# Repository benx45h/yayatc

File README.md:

# YAYATC- Yet Another YATC
### A new temperature controller, because the YATC links were broken.

YAYATC is a temperature controller designed to heat or cool things to any temperature, within reason. YAYATC can handle either a 10k NTC thermistor or the 1-wire thing from Sparkfun as a temperature sensor. As long as only one is plugged in, YAYATC will automatically detect which to use.
No external power supply is needed- all circuitry is powered directly from the wall.  

The goal here was to minimize design time, and other temperature controllers may have better performance, cheaper BOMs, easier assembly, etc.

Revision 1 has not been tested. If you want to make one anyways, go ahead.

Revision 1 known issues:
~~ - No way to tell if temperature is positive or negative ~~  
~~ - Only 2 digits. No way to display temperatures above 100. ~~

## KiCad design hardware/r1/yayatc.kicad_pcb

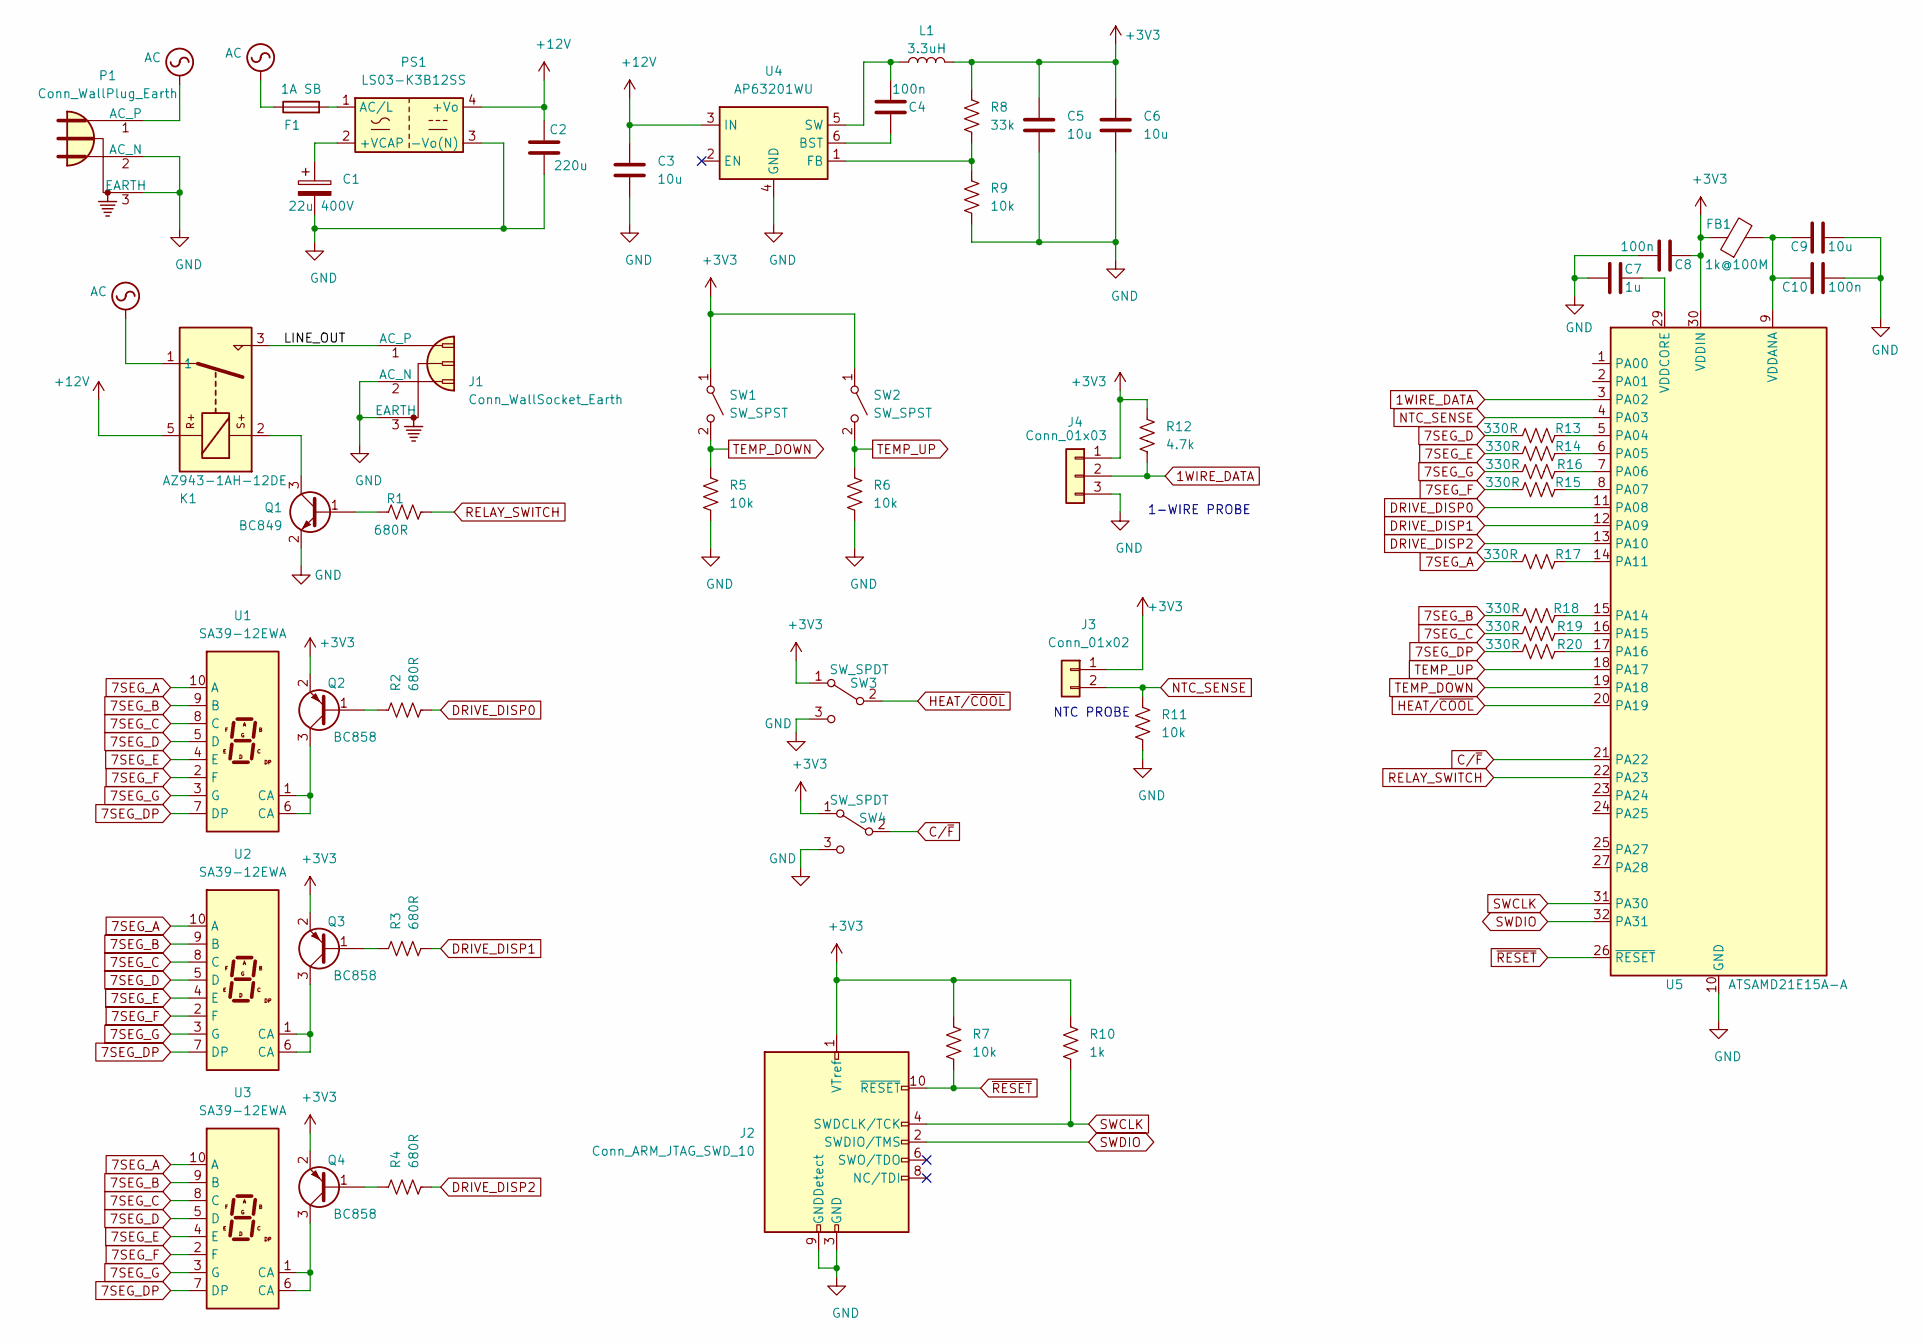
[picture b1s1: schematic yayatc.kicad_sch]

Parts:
C1: 22u 400V; CP_Radial_D12.5mm_P5.00mm; Digikey-PN 493-5875-ND
C2: 220u; CP_Radial_D6.3mm_P2.50mm; Digikey-PN 732-8797-1-ND
C3, C5, C6, C9: 10u; C_0805_2012Metric_Pad1.18x1.45mm_HandSolder; Digikey-PN 1276-6455-1-ND
C4, C8, C10: 100n; C_0603_1608Metric_Pad1.08x0.95mm_HandSolder; Digikey-PN 1276-CL10B104KB8NNNLCT-ND
C7: 1u; C_0603_1608Metric_Pad1.08x0.95mm_HandSolder; Digikey-PN 1276-1102-1-ND
F1: 1A SB; 0697H1000-02; Digikey-PN 507-1927-1-ND
FB1: 1k@100M; L_0603_1608Metric_Pad1.05x0.95mm_HandSolder; Digikey-PN 587-1895-1-ND
J1: Conn_WallSocket_Earth; SolderWire-1sqmm_1x03_P5.4mm_D1.4mm_OD2.7mm; Digikey-PN Q337-ND
J2: Conn_ARM_JTAG_SWD_10; PinHeader_2x05_P1.27mm_Vertical; Digikey-PN 1849-PR20B05VBDN-ND
J3: Conn_01x02; JST_PH_B2B-PH-K_1x02_P2.00mm_Vertical; Digikey-PN 455-1704-ND
J4: Conn_01x03; JST_PH_B3B-PH-K_1x03_P2.00mm_Vertical; Digikey-PN 455-1704-ND
K1: AZ943-1AH-12DE; Relay_AZ945_A; Digikey-PN 2487-AZ943-1AH-12DE-ND
L1: 3.3uH; L_0805_2012Metric_Pad1.15x1.40mm_HandSolder; Digikey-PN 445-6759-1-ND
P1: Conn_WallPlug_Earth; 703W-00-54; Digikey-PN Q220-ND
PS1: LS03-K3B12SS; LSxx-K3BxxSS; Digikey-PN 2725-LS03-K3B12SS-ND
Q1: BC849; SOT-23; Digikey-PN BC849B-TPMSCT-ND
Q2, Q3, Q4: BC858; SOT-23; Digikey-PN BC858CLT3GOSCT-ND
R1, R2, R3, R4: 680R; R_0603_1608Metric_Pad0.98x0.95mm_HandSolder; Digikey-PN RR08P680DCT-ND
R5, R6, R7, R9, R11: 10k; R_0603_1608Metric_Pad0.98x0.95mm_HandSolder; Digikey-PN RR08P10.0KDCT-ND
R8: 33k; R_0603_1608Metric_Pad0.98x0.95mm_HandSolder; Digikey-PN 311-33.0KHRCT-ND
R10: 1k; R_0603_1608Metric_Pad0.98x0.95mm_HandSolder; Digikey-PN RR08P1.0KDCT-ND
R12: 4.7k; R_0603_1608Metric_Pad0.98x0.95mm_HandSolder; Digikey-PN 311-4.70KHRCT-ND
R13, R14, R15, R16, R17, R18, R19, R20: 330R; R_0603_1608Metric_Pad0.98x0.95mm_HandSolder; Digikey-PN 311-330HRCT-ND
SW1, SW2: SW_SPST; SW_PUSH_6mm_H13mm; Digikey-PN 450-1642-ND
SW3, SW4: SW_SPDT; OS102011MS2Q*; Digikey-PN CKN9565-ND
U1, U2, U3: SA39-12EWA; Sx39-1xxxxx; Digikey-PN 3011-SA39-12EWA-ND
U4: AP63201WU; TSOT-23-6; Digikey-PN 31-AP62301Z6-7CT-ND
U5: ATSAMD21E15A-A; TQFP-32_7x7mm_P0.8mm; Digikey-PN ATSAMD21E17L-AFTCT-ND

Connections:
1WIRE_DATA: J4.2, R12.2, U5.3 (PA02)
7SEG_A: R17.1, U1.10 (A), U2.10 (A), U3.10 (A)
7SEG_B: R18.1, U1.9 (B), U2.9 (B), U3.9 (B)
7SEG_C: R19.1, U1.8 (C), U2.8 (C), U3.8 (C)
7SEG_D: R13.1, U1.5 (D), U2.5 (D), U3.5 (D)
7SEG_DP: R20.1, U1.7 (DP), U2.7 (DP), U3.7 (DP)
7SEG_E: R14.1, U1.4 (E), U2.4 (E), U3.4 (E)
7SEG_F: R15.1, U1.2 (F), U2.2 (F), U3.2 (F)
7SEG_G: R16.1, U1.3 (G), U2.3 (G), U3.3 (G)
+3V3: C5.1, C6.1, C8.1, FB1.1, J2.1 (VTref), J3.1, J4.1, L1.2, Q2.2 (E), Q3.2 (E), Q4.2 (E), R7.1, R8.1, R10.1, R12.1, SW1.1 (A), SW2.1 (A), SW3.1 (A), SW4.1 (A), U5.30 (VDDIN)
+12V: C2.1, C3.1, K1.5, PS1.4 (+Vo), U4.3 (IN)
/LINE_OUT: J1.1 (AC_P), K1.3
AC: F1.1, K1.1, P1.1 (AC_P)
C/~F: SW4.2 (B), U5.21 (PA22)
DRIVE_DISP0: R2.2, U5.11 (PA08)
DRIVE_DISP1: R3.2, U5.12 (PA09)
DRIVE_DISP2: R4.2, U5.13 (PA10)
GND: C1.2, C2.2, C3.2, C5.2, C6.2, C7.1, C8.2, C9.2, C10.2, J1.2 (AC_N), J1.3 (EARTH), J2.3 (GND), J2.5 (GND), J2.9 (GNDDetect), J4.3, P1.2 (AC_N), P1.3 (EARTH), PS1.3 (-Vo(N)), Q1.2 (E), R5.2, R6.2, R9.2, R11.2, SW3.3 (C), SW4.3 (C), U4.4 (GND), U5.10 (GND), U5.28 (GND)
HEAT/~COOL: SW3.2 (B), U5.20 (PA19)
NTC_SENSE: J3.2, R11.1, U5.4 (PA03)
unnamed: C1.1, PS1.2 (+VCAP)
unnamed: C4.1, U4.6 (BST)
unnamed: C4.2, L1.1, U4.5 (SW)
unnamed: C7.2, U5.29 (VDDCORE)
unnamed: C9.1, C10.1, FB1.2, U5.9 (VDDANA)
unnamed: F1.2, PS1.1 (AC/L)
unnamed: K1.2, Q1.3 (C)
unnamed: Q1.1 (B), R1.1
unnamed: Q2.1 (B), R2.1
unnamed: Q2.3 (C), U1.1 (CA), U1.6 (CA)
unnamed: Q3.1 (B), R3.1
unnamed: Q3.3 (C), U2.1 (CA), U2.6 (CA)
unnamed: Q4.1 (B), R4.1
unnamed: Q4.3 (C), U3.1 (CA), U3.6 (CA)
unnamed: R8.2, R9.1, U4.1 (FB)
unnamed: R13.2, U5.5 (PA04)
unnamed: R14.2, U5.6 (PA05)
unnamed: R15.2, U5.8 (PA07)
unnamed: R16.2, U5.7 (PA06)
unnamed: R17.2, U5.14 (PA11)
unnamed: R18.2, U5.15 (PA14)
unnamed: R19.2, U5.16 (PA15)
unnamed: R20.2, U5.17 (PA16)
RELAY_SWITCH: R1.2, U5.22 (PA23)
SWCLK: J2.4 (SWDCLK/TCK), R10.2, U5.31 (PA30)
SWDIO: J2.2 (SWDIO/TMS), U5.32 (PA31)
TEMP_DOWN: R5.1, SW1.2 (B), U5.19 (PA18)
TEMP_UP: R6.1, SW2.2 (B), U5.18 (PA17)
no_connect_56: J2.6 (SWO/TDO)
no_connect_57: J2.8 (NC/TDI)
no_connect_58: U4.2 (EN)
~RESET: J2.10 (~RESET~), R7.2, U5.26 (~RESET)

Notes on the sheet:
NTC PROBE
1-WIRE PROBE

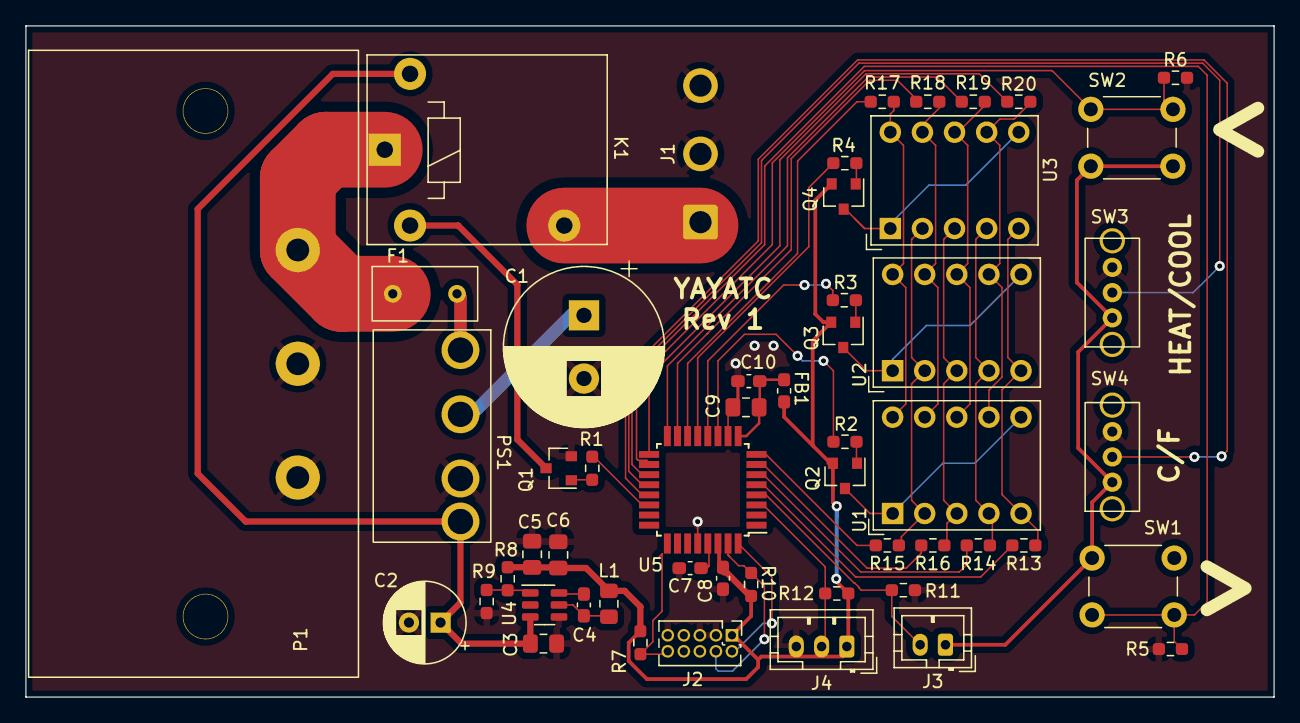
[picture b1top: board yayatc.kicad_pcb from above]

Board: 2 copper layers, 98.8 x 53.1 mm, 53 parts (0 on the bottom side), 49 nets.

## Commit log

2021-01-05 Rev 1 complete
2021-01-05 Added README
2021-01-05 Clarifications
2021-01-19 Removed nonissues
